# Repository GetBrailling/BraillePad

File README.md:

BraillePad
----------

BraillePad is a project with the goal of making good input technologies available for the visually impared and ergonomically strained users of modern technology. Currently the project is in an early stage with one prototype built and the direction of action is to find out user needs, collect valuable user feedback, find the best design solutions for the multitude of applications, create blueprints for the second prototype, look for partnerships, elaborate on the sequence of developments and discuss market entry point and our business model..

Hardware
--------

The current version of BraillePad runs on Arduino Leonardo and compatibles. The interface consists of six simple buttons.

Software
--------

How to compile?

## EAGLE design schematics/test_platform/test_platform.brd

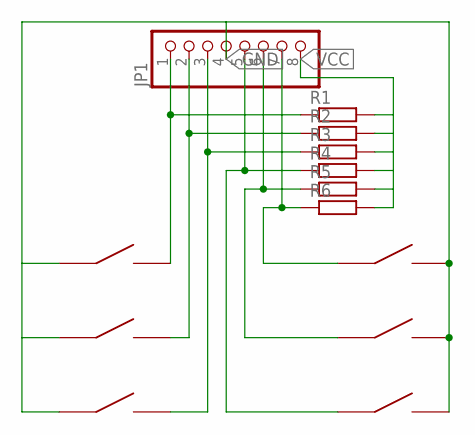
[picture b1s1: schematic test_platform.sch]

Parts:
JP1: PINHD-1X8BIG; 1X08-BIG
R1, R2, R3, R4, R5, R6: R-EU_M0805; M0805
U$1, U$2, U$3, U$4, U$5, U$6: SMT_BUTTON; SMT-BUTTON

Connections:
GND: JP1.4, U$1.A1 (A), U$1.A2 (A), U$2.A1 (A), U$2.A2 (A), U$3.A1 (A), U$3.A2 (A), U$4.B1 (B), U$4.B2 (B), U$5.B1 (B), U$5.B2 (B), U$6.B1 (B), U$6.B2 (B)
unnamed: JP1.1, R1.1, U$1.B1 (B), U$1.B2 (B)
unnamed: JP1.2, R2.1, U$2.B1 (B), U$2.B2 (B)
unnamed: JP1.3, R3.1, U$3.B1 (B), U$3.B2 (B)
unnamed: JP1.5, R4.1, U$4.A1 (A), U$4.A2 (A)
unnamed: JP1.6, R5.1, U$5.A1 (A), U$5.A2 (A)
unnamed: JP1.7, R6.1, U$6.A1 (A), U$6.A2 (A)
VCC: JP1.8, R1.2, R2.2, R3.2, R4.2, R5.2, R6.2

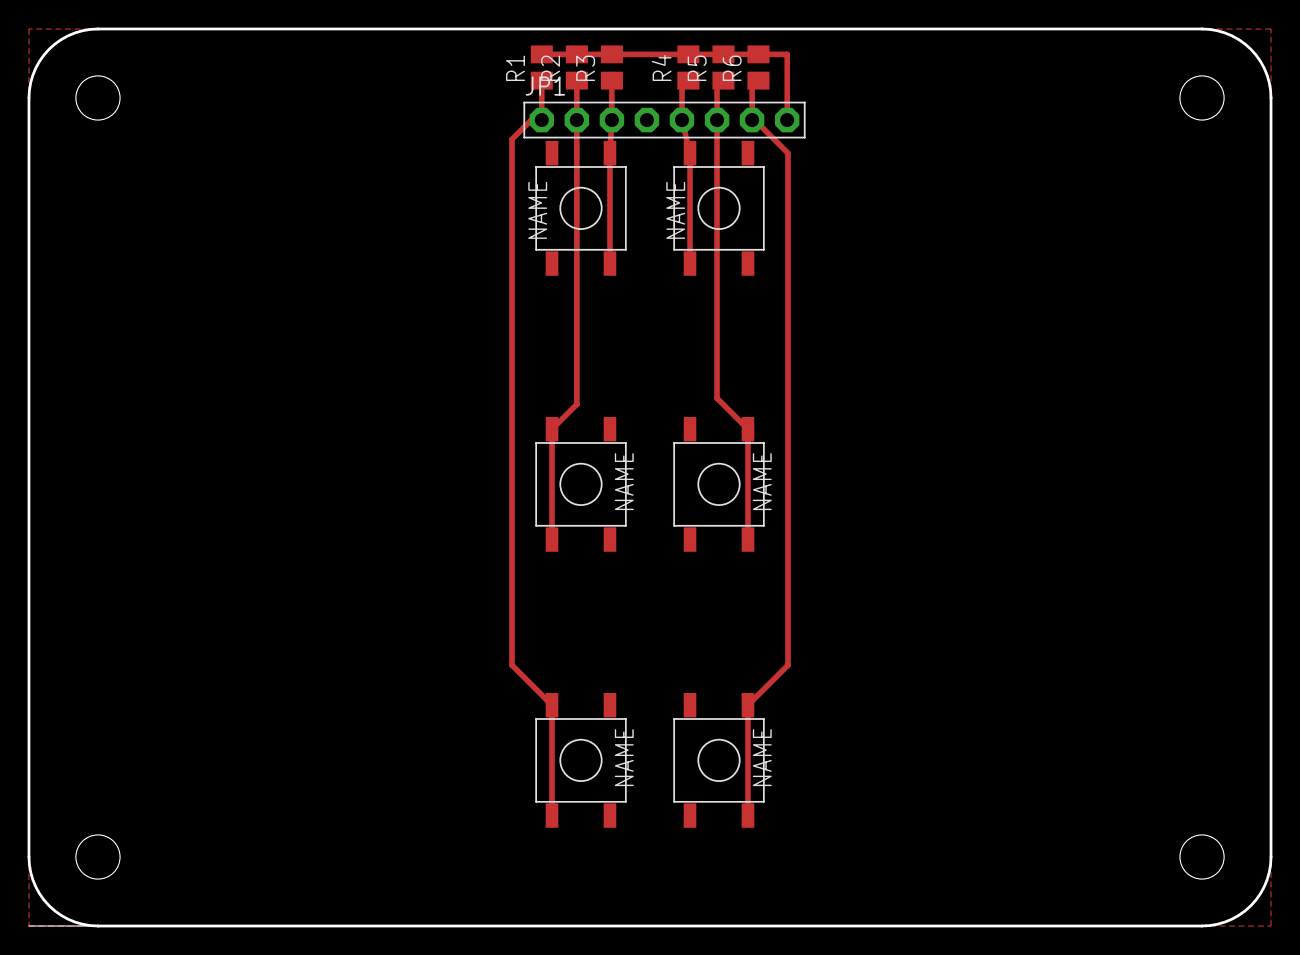
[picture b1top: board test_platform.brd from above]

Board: 2 copper layers, 90.0 x 65.0 mm, 13 parts (0 on the bottom side), 8 nets.

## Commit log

2014-11-20 initial commit, some improvements done after TehnoHack
2014-11-21 some circuit desing and mechanical desing done on the test platform
2014-11-21 added enable48 introduction to documentation
2014-11-21 Update introduction.md
    The version which I submitted to Garage48
2014-11-22 test platform ready for production, except for button footprints
2014-11-23 Removed previous list of developers, updated "direction of action"
2014-11-24 circuit for testplatform done
2014-11-25 testplatform done, image added
2014-11-25 another image added
2014-11-29 Added design files
2014-11-29 version 2.0 with working newline and spacebar
2014-11-30 punctuation, capitals, and number perfected
2014-11-30 let's commit to being open source!
2014-12-03 Added latest Brailling Designs
2014-12-08 added tag for version 2.0 of the software
2014-12-08 refactored the software to use interrupts instead of polling loop
2014-12-08 a bit of explanation
2014-12-10 key repetition implemented
